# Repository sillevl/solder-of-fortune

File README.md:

# solder-of-fortune

[![CC BY-SA 4.0][cc-by-sa-shield]][cc-by-sa]

PCB Soldering challenges

## License

This work is licensed under a
[Creative Commons Attribution-ShareAlike 4.0 International License][cc-by-sa].

[![CC BY-SA 4.0][cc-by-sa-image]][cc-by-sa]

[cc-by-sa]: http://creativecommons.org/licenses/by-sa/4.0/
[cc-by-sa-image]: https://licensebuttons.net/l/by-sa/4.0/88x31.png
[cc-by-sa-shield]: https://img.shields.io/badge/License-CC%20BY--SA%204.0-lightgrey.svg

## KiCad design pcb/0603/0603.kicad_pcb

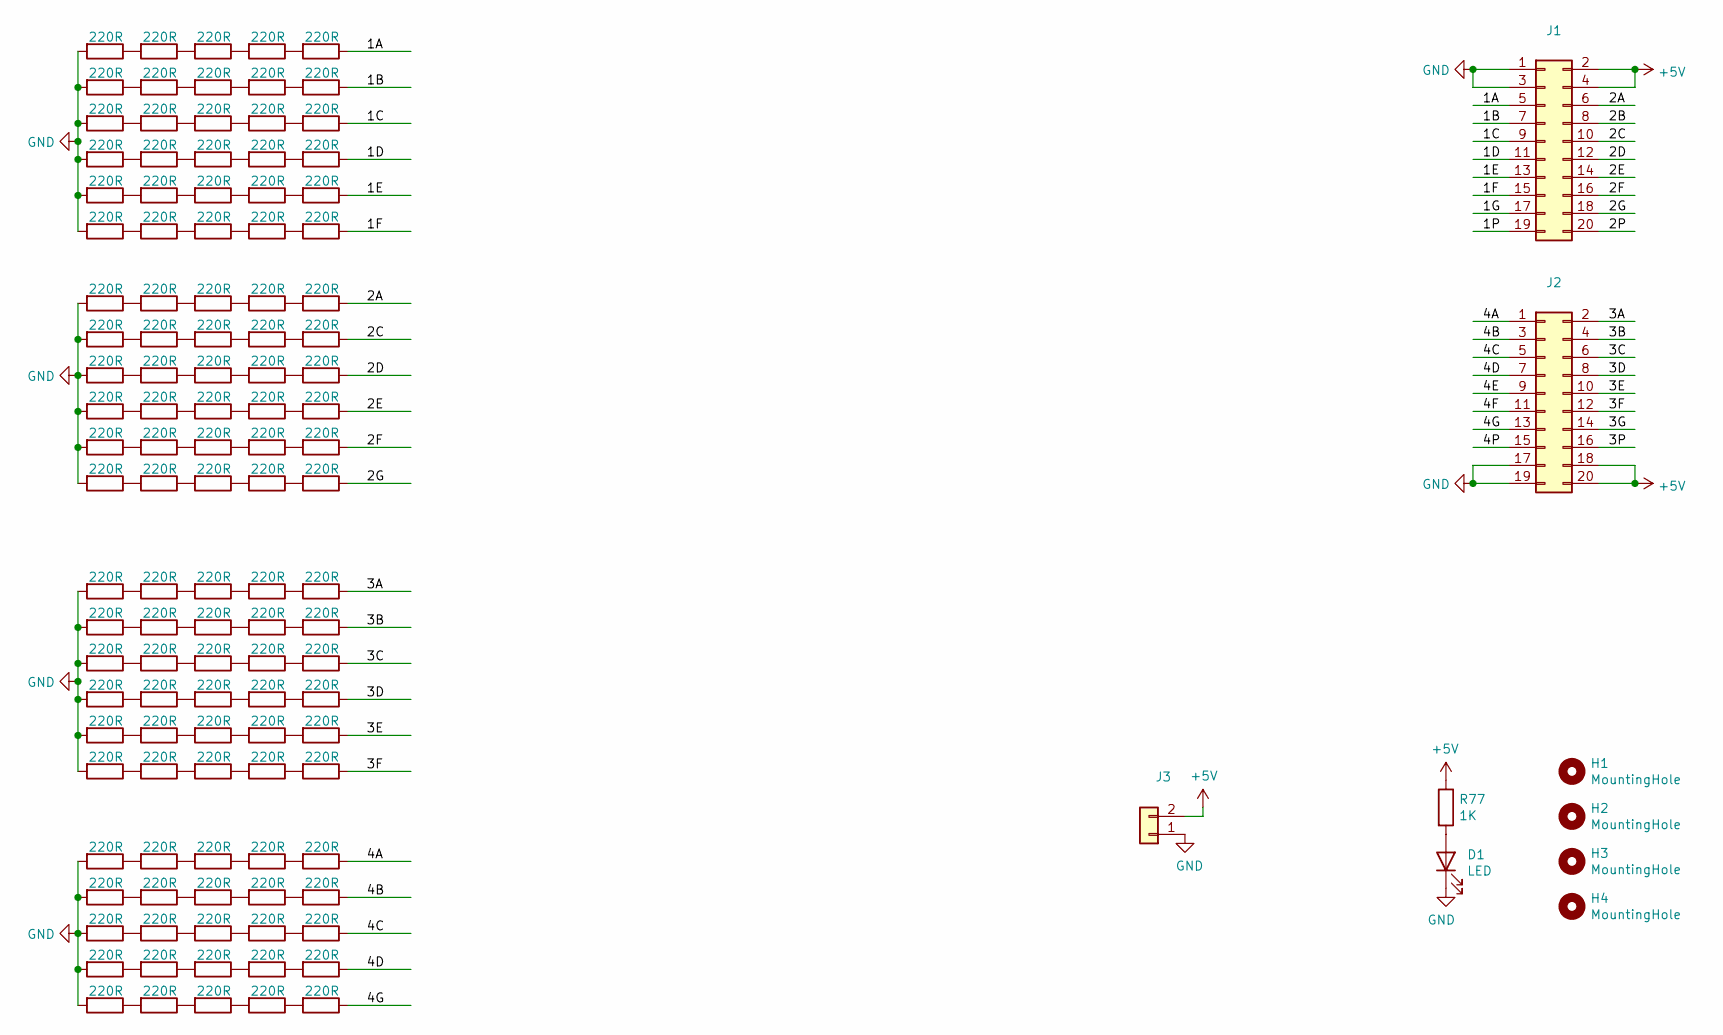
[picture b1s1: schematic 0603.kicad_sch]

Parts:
D1: LED; LED_1206_3216Metric_Pad1.42x1.75mm_HandSolder
H1, H2, H3, H4: MountingHole; MountingHole_3.2mm_M3
J1, J2: Conn_02x10_Odd_Even; PinHeader_2x10_P2.54mm_Vertical
J3: Conn_01x02; PinHeader_1x02_P2.54mm_Horizontal
R1, R2, R3, R5, R6, R7, R10, R11, R12, R17, R20, R21, R22, R24, R25, R26, R29, R30, R39, R40, R41, R43, R44, R45, R49, R50, R55, R58, R59, R60, R62, R63, R64, R67, R68, R69, R78, R79, R80, R82, R83, R84, R89, R94, R97, R98, R99, R100, R104, R105, R106, R107, R108, R109, R113, R114, R115, R116, R117, R118: 220R; R_0603_1608Metric_Pad0.98x0.95mm_HandSolder
R8, R9, R13, R14, R15, R16, R18, R19, R27, R28, R31, R32, R33, R34, R35, R36, R37, R38, R46, R47, R48, R51, R52, R53, R54, R56, R57, R65, R66, R70, R71, R72, R73, R74, R75, R76, R85, R86, R87, R88, R90, R91, R92, R93, R95, R96, R101, R102, R103, R110, R111, R112, R119, R120, R121: 220R; R_0603_1608Metric
R77: 1K; R_1206_3216Metric_Pad1.42x1.75mm_HandSolder

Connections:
+5V: J1.2, J1.4, J2.18, J2.20, J3.2, R77.1
/1A: J1.5, R78.1
/1B: J1.7, R79.1
/1C: J1.9, R113.1
/1D: J1.11, R114.1
/1E: J1.13, R115.1
/1F: J1.15, R116.1
/1G: J1.17
/1P: J1.19
/2A: J1.6, R80.1
/2B: J1.8
/2C: J1.10, R82.1
/2D: J1.12, R83.1
/2E: J1.14, R84.1
/2F: J1.16, R117.1
/2G: J1.18, R118.1
/2P: J1.20
/3A: J2.2, R85.1
/3B: J2.4, R86.1
/3C: J2.6, R119.1
/3D: J2.8, R120.1
/3E: J2.10, R121.1
/3F: J2.12, R90.1
/3G: J2.14
/3P: J2.16
/4A: J2.1, R91.1
/4B: J2.3, R92.1
/4C: J2.5, R93.1
/4D: J2.7, R95.1
/4E: J2.9
/4F: J2.11
/4G: J2.13, R96.1
/4P: J2.15
unnamed: D1.2 (A), R77.2
unnamed: R1.1, R20.2
unnamed: R2.1, R21.2
unnamed: R10.1, R49.2
unnamed: R11.1, R50.2
unnamed: R12.1, R55.2
unnamed: R13.1, R32.2
unnamed: R14.1, R33.2
unnamed: R15.1, R34.2
unnamed: R16.1, R35.2
unnamed: R17.1, R67.2
unnamed: R18.1, R37.2
unnamed: R19.1, R38.2
unnamed: R20.1, R39.2
unnamed: R21.1, R40.2
unnamed: R22.1, R41.2
unnamed: R3.1, R22.2
unnamed: R24.1, R43.2
unnamed: R5.1, R24.2
unnamed: R25.1, R44.2
unnamed: R6.1, R25.2
unnamed: R26.1, R45.2
unnamed: R7.1, R26.2
unnamed: R27.1, R46.2
unnamed: R8.1, R27.2
unnamed: R28.1, R47.2
unnamed: R9.1, R28.2
unnamed: R29.1, R68.2
unnamed: R30.1, R69.2
unnamed: R31.1, R74.2
unnamed: R32.1, R51.2
unnamed: R33.1, R52.2
unnamed: R34.1, R53.2
unnamed: R35.1, R54.2
unnamed: R36.1, R87.2
unnamed: R37.1, R56.2
unnamed: R38.1, R57.2
unnamed: R39.1, R58.2
unnamed: R40.1, R59.2
unnamed: R41.1, R60.2
unnamed: R43.1, R62.2
unnamed: R44.1, R63.2
unnamed: R45.1, R64.2
unnamed: R46.1, R65.2
unnamed: R47.1, R66.2
unnamed: R48.1, R88.2
unnamed: R49.1, R89.2
unnamed: R50.1, R94.2
unnamed: R51.1, R70.2
unnamed: R52.1, R71.2
unnamed: R53.1, R72.2
unnamed: R54.1, R73.2
unnamed: R55.1, R97.2
unnamed: R56.1, R75.2
unnamed: R57.1, R76.2
unnamed: R58.1, R78.2
unnamed: R59.1, R79.2
unnamed: R60.1, R80.2
unnamed: R62.1, R82.2
unnamed: R63.1, R83.2
unnamed: R64.1, R84.2
unnamed: R65.1, R85.2
unnamed: R66.1, R86.2
unnamed: R67.1, R98.2
unnamed: R68.1, R99.2
unnamed: R70.1, R90.2
unnamed: R71.1, R91.2
unnamed: R72.1, R92.2
unnamed: R73.1, R93.2
unnamed: R75.1, R95.2
unnamed: R76.1, R96.2
unnamed: R100.1, R109.2
unnamed: R69.1, R100.2
unnamed: R101.1, R110.2
unnamed: R74.1, R101.2
unnamed: R102.1, R111.2
unnamed: R87.1, R102.2
unnamed: R103.1, R112.2
unnamed: R88.1, R103.2
unnamed: R104.1, R113.2
unnamed: R89.1, R104.2
unnamed: R105.1, R114.2
unnamed: R94.1, R105.2
unnamed: R106.1, R115.2
unnamed: R97.1, R106.2
unnamed: R107.1, R116.2
unnamed: R98.1, R107.2
unnamed: R108.1, R117.2
unnamed: R99.1, R108.2
unnamed: R109.1, R118.2
unnamed: R110.1, R119.2
unnamed: R111.1, R120.2
unnamed: R112.1, R121.2

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
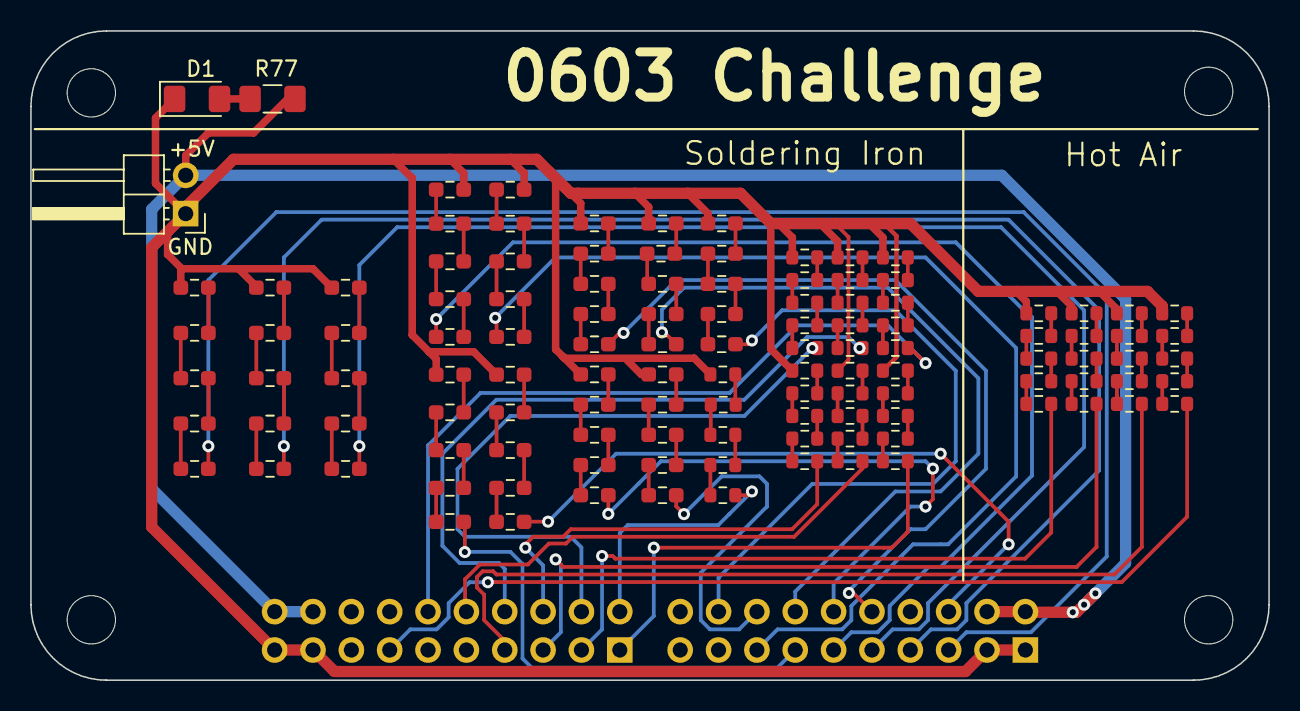
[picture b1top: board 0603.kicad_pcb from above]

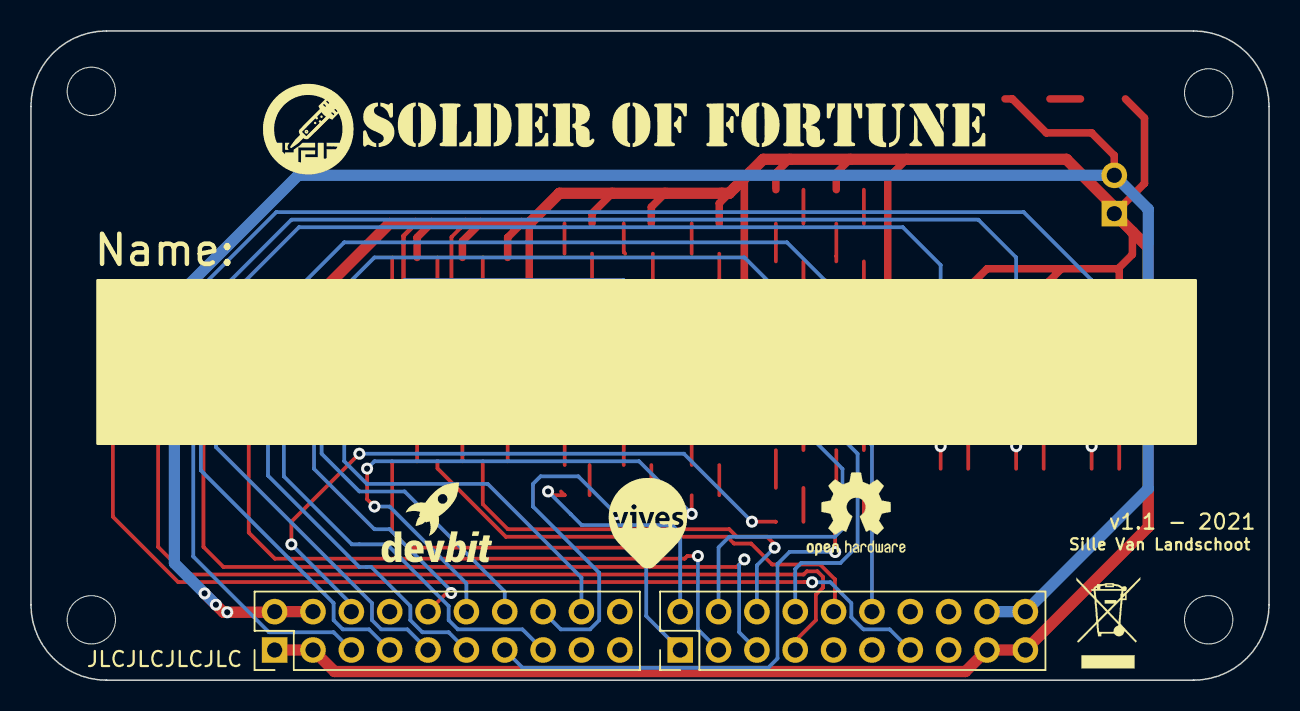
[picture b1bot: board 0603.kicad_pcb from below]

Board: 2 copper layers, 82.0 x 43.0 mm, 124 parts (2 on the bottom side), 118 nets.

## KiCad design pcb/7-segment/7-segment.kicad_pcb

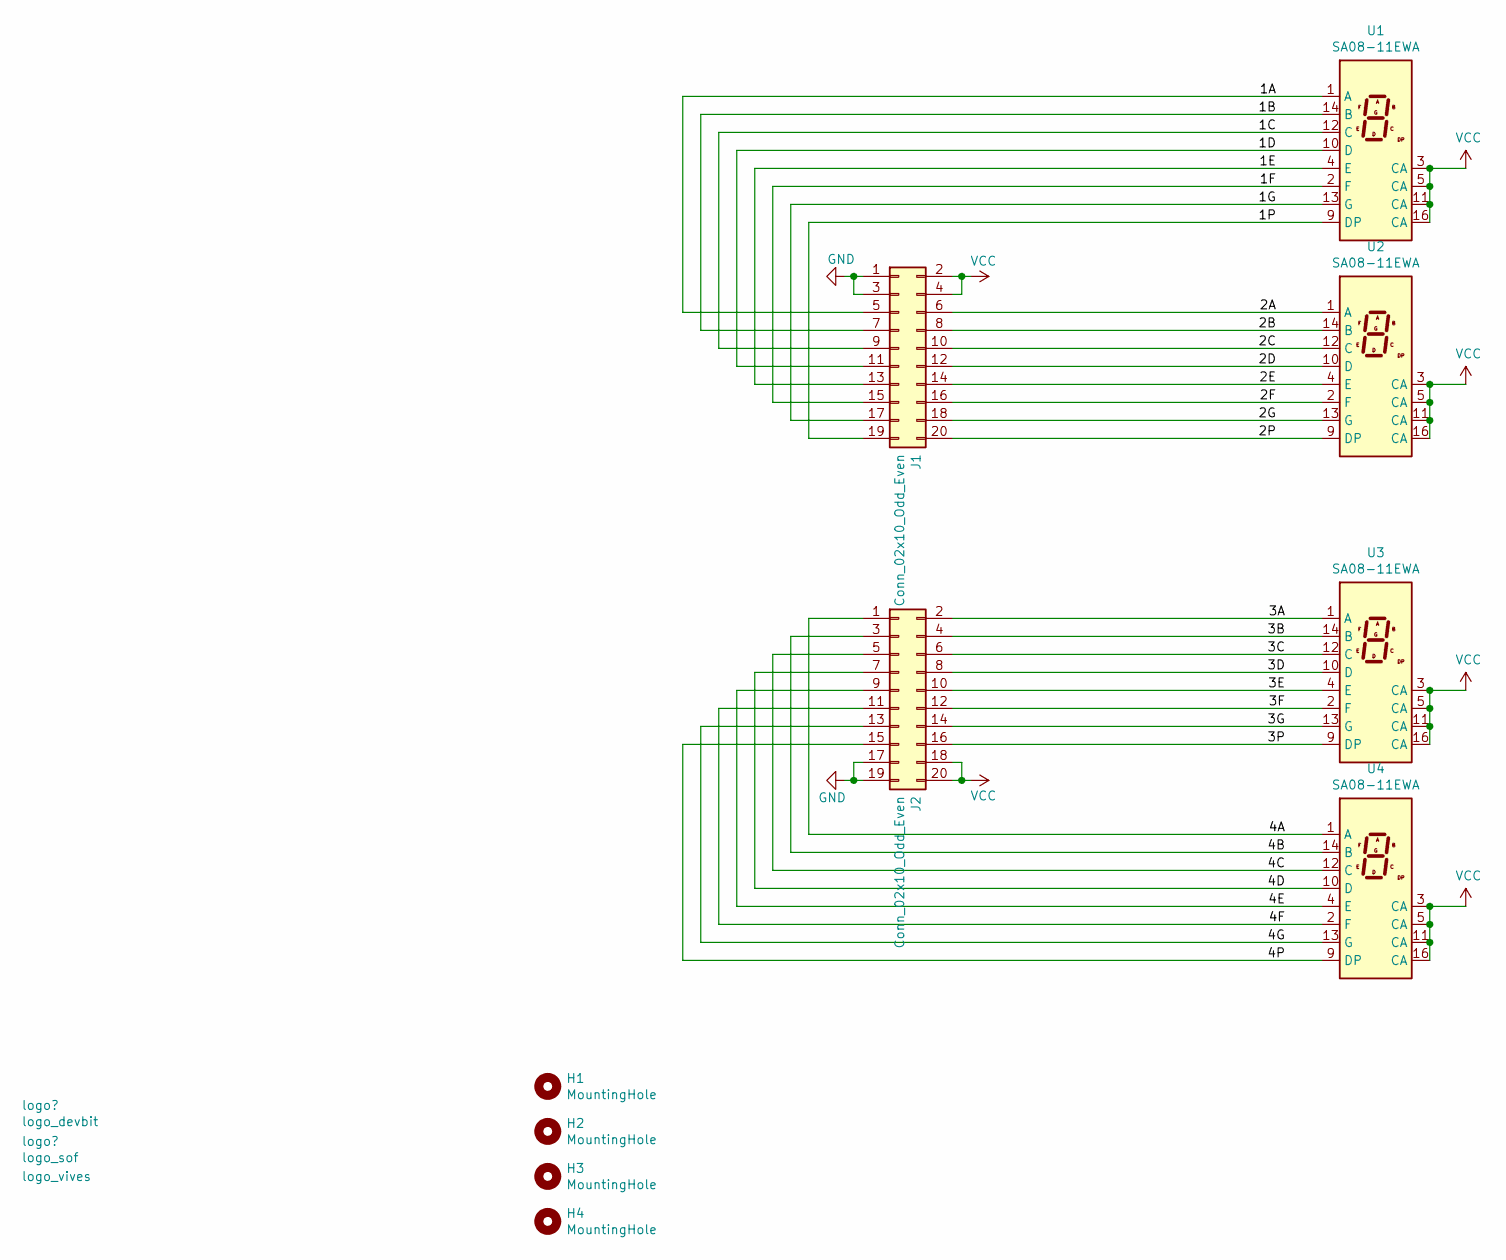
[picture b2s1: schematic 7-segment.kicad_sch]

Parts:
H1, H2, H3, H4: MountingHole; MountingHole_3.2mm_M3
J1, J2: Conn_02x10_Odd_Even; PinSocket_2x10_P2.54mm_Vertical
U1, U2, U3, U4: SA08-11EWA

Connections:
/1A: J1.5, U1.1 (A)
/1B: J1.7, U1.14 (B)
/1C: J1.9, U1.12 (C)
/1D: J1.11, U1.10 (D)
/1E: J1.13, U1.4 (E)
/1F: J1.15, U1.2 (F)
/1G: J1.17, U1.13 (G)
/1P: J1.19, U1.9 (DP)
/2A: J1.6, U2.1 (A)
/2B: J1.8, U2.14 (B)
/2C: J1.10, U2.12 (C)
/2D: J1.12, U2.10 (D)
/2E: J1.14, U2.4 (E)
/2F: J1.16, U2.2 (F)
/2G: J1.18, U2.13 (G)
/2P: J1.20, U2.9 (DP)
/3A: J2.2, U3.1 (A)
/3B: J2.4, U3.14 (B)
/3C: J2.6, U3.12 (C)
/3D: J2.8, U3.10 (D)
/3E: J2.10, U3.4 (E)
/3F: J2.12, U3.2 (F)
/3G: J2.14, U3.13 (G)
/3P: J2.16, U3.9 (DP)
/4A: J2.1, U4.1 (A)
/4B: J2.3, U4.14 (B)
/4C: J2.5, U4.12 (C)
/4D: J2.7, U4.10 (D)
/4E: J2.9, U4.4 (E)
/4F: J2.11, U4.2 (F)
/4G: J2.13, U4.13 (G)
/4P: J2.15, U4.9 (DP)
GND: J1.1, J1.3, J2.17, J2.19
VCC: J1.2, J1.4, J2.18, J2.20, U1.3 (CA), U1.5 (CA), U1.11 (CA), U1.16 (CA), U2.3 (CA), U2.5 (CA), U2.11 (CA), U2.16 (CA), U3.3 (CA), U3.5 (CA), U3.11 (CA), U3.16 (CA), U4.3 (CA), U4.5 (CA), U4.11 (CA), U4.16 (CA)

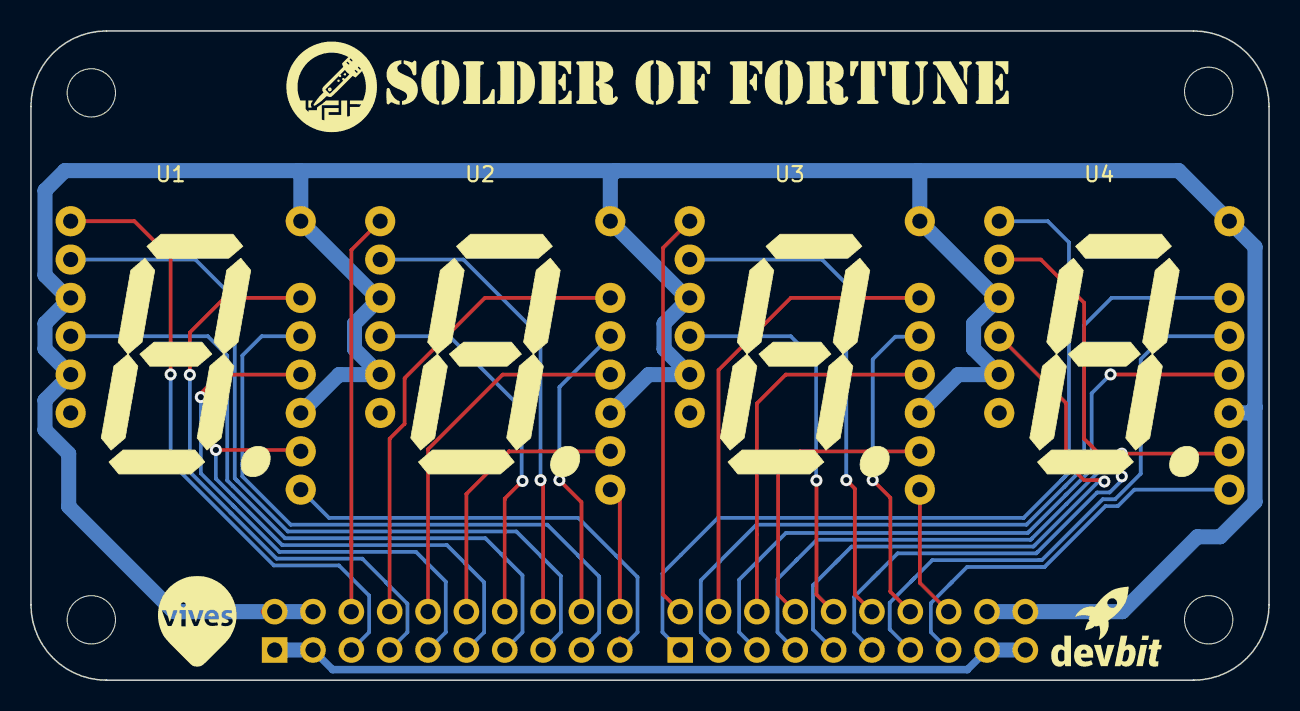
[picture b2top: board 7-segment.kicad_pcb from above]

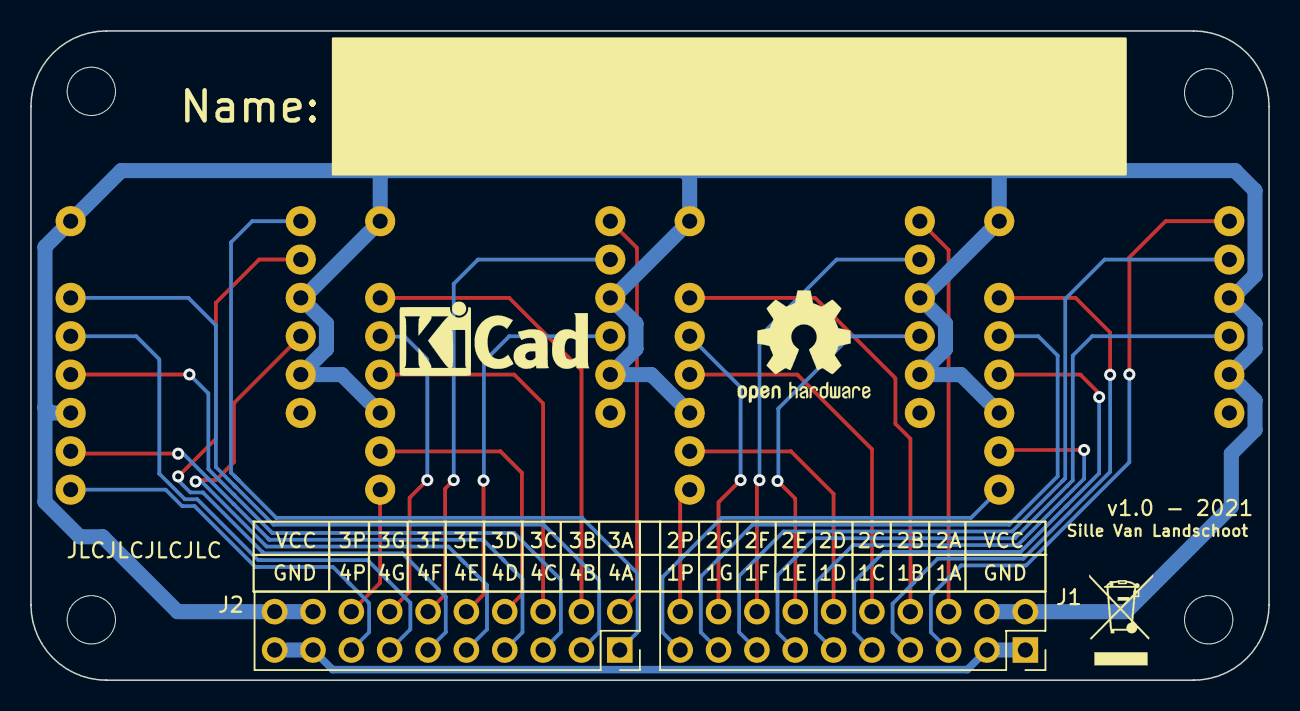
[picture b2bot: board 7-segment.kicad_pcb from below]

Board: 2 copper layers, 82.0 x 43.0 mm, 10 parts (2 on the bottom side), 34 nets.

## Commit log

2021-02-18 add gitignore file
2021-02-18 add intial projects 7 segment 1206 0805 0603 0402
2021-03-26 fix routing in resistor pcb's
2021-03-26 setup docs with vuepress
2021-03-26 fix public files not copied in build
2021-03-26 add startAt feature to youtube video component
2021-03-26 rename introduction file
2021-03-26 add 7-segment chapter
2021-03-26 update introduction
2021-03-26 update introductions
2021-03-26 update challenges
2021-03-26 ignore dist/build directory
2021-03-26 add netlify status badge
2021-03-26 fix insecure links
2021-03-26 update netlify badge position
2021-03-31 fix library references
